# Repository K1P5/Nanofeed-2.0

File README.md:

# Nanofeed-2.0
Miniature Micro-controlled Feed Auger with Tank 

THIS IS A WORK IN PROGRESS! Thingiverse link: https://www.thingiverse.com/thing:4743999
------------------------------------------------------------------------------------------------------
Historic link to the orginal design, the Feederpi! 
https://www.thingiverse.com/thing:2947556

------------------------------------------------------------------------------------------------------------------------
I will continue to support this design based on user feedback; this means if no one is particularly interested, I will update only as I create new revisions to meet my personal project needs. If you have any questions, concerns, comments please feel free to message me and I will get back to you!

Remaining Uploads:

BOM
Assembly Instructions
PCB Schematic (Via Github link^^^)
Arduino Code (^^^)
Reference Build Images (^^^)

------------------------------------------------------------------------------------------------------------------------

This is the updated and improved miniature all-in-one material auger with integrated storage tank. Better torque, RTC (real time clock) control, Github hosted design/resource files, script(s), PCB files, etc! Based on an Arduino Nano, DRV8825 stepper driver, and a DS3231 RTC breakout, this unit is intended to be a low cost, fun, and DIY solution to automating your low-scale material handling (feeding) needs! 

Operation is simple; Fill the integrated tank with the material of choice (flake/granular material ~3-5mm Dia. MAX). Mount the unit in the location/orientation of choice, and provide 12V DC power via the rear power port. The Nanofeed will await a button press, upon which the auger will perform an adjustable feed cycle (adjustable via IDE). When the cycle is complete, the RTC module will begin a twenty-four (24) hour delay cycle (adjustable via IDE). After the elapsed time has passed, the Nanofeed will dispense an additional feed volume, resetting the RTC timer once again to continue your established, timed feed cycle. 

This design is the latest revision of my earlier Feederpi, the Pi Zero controlled feed system, with many improved features. 

-Arduino Nano powered; allows for a simple, low-cost microcontroller to handle automation, no need to waste a much more valuable and resource-intensive Pi.
 
-The belt path has been revised, ensuring sufficient torque transfer even when dispensing tough materials. 

-The original continuous-servo was replaced with a 4-wire miniature stepper motor, controlled via the onboard DRV8825. 

-Critical components are now mounted and assembled via "mounting cards"; Easy to print, assemble and disassemble the cards allow easy access and transfer of critical components. 

-Simplified and easy-to-print design ensures most if not all home printer solutions will have no issue reproducing the design in your own corner of the world. 

------------------------------------------------------------------------------------------------------------------------
Please Note!

This design utilizes a prototyped PCB, check the included images to understand the scope of development work involved. There "should" be sufficient interior volume within the PCB containment area, so it may be possible to revise the PCB mounting card to instead utilize a prototyping breadboard and related hardware. Check the related Parasolid file(s) to revise as needed.

I will release my original bare PCB, which will be available off of PCBWay for those that would like a more accessible option. The schematic, Gerber files and BOM will also be uploaded to Github, as I continue distributing this design. Please either check back here for the Github link or message me directly!

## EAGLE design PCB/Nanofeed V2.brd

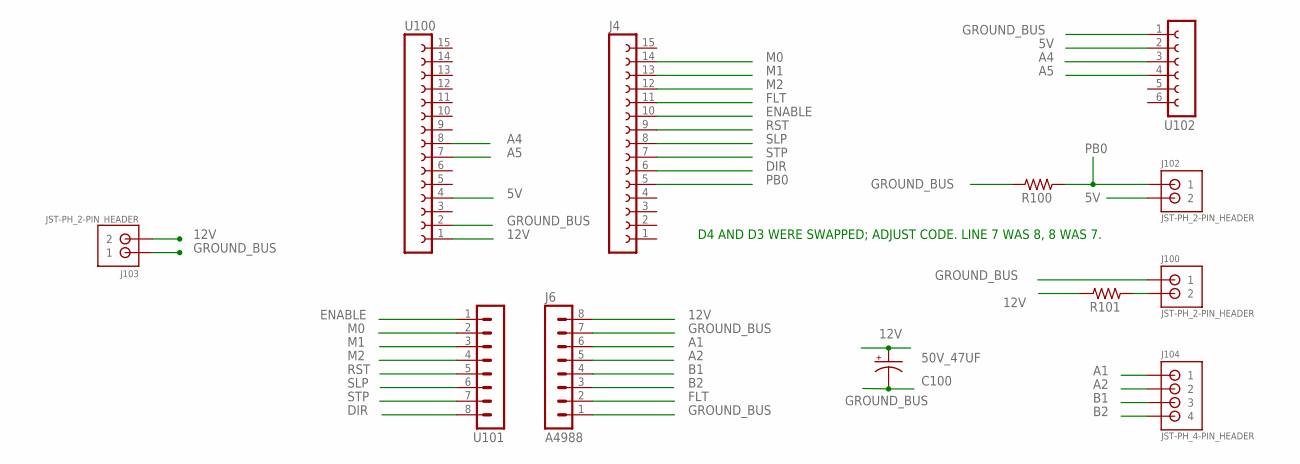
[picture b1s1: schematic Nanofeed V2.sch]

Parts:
C100: 50V_47UF; PANASONIC_D
J4: FE15-1; FE15
J6: A4988; MA08-1
J100, J102, J103: JST-PH_2-PIN_HEADER; JST_B2B-PH_HEADER
J104: JST-PH_4-PIN_HEADER; JST_B4B-PH_HEADER
R100, R101: R_5025; R5025
U100: FE15-1; FE15
U101: MA08-1
U102: FE06-1; FE06

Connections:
5V: J102.P2 (2), U100.4, U102.2
12V: C100.+, J6.8, J103.P2 (2), R101.2, U100.1
A1: J6.6, J104.P1 (1)
A2: J6.5, J104.P2 (2)
A4: U100.8, U102.3
A5: U100.7, U102.4
B1: J6.4, J104.P3 (3)
B2: J6.3, J104.P4 (4)
DIR: J4.6, U101.8
ENABLE: J4.10, U101.1
FLT: J4.11, J6.2
GROUND_BUS: C100.-, J6.1, J100.P1 (1), J103.P1 (1), R100.2, U100.2, U102.1
M0: J4.14, U101.2
M1: J4.13, U101.3
M2: J4.12, U101.4
unnamed: J100.P2 (2), R101.1
PB0: J4.5, J102.P1 (1), R100.1
RST: J4.9, U101.5
SLP: J4.8, U101.6
STP: J4.7, U101.7

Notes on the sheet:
D4 AND D3 WERE SWAPPED; ADJUST CODE. LINE 7 WAS 8, 8 WAS 7.

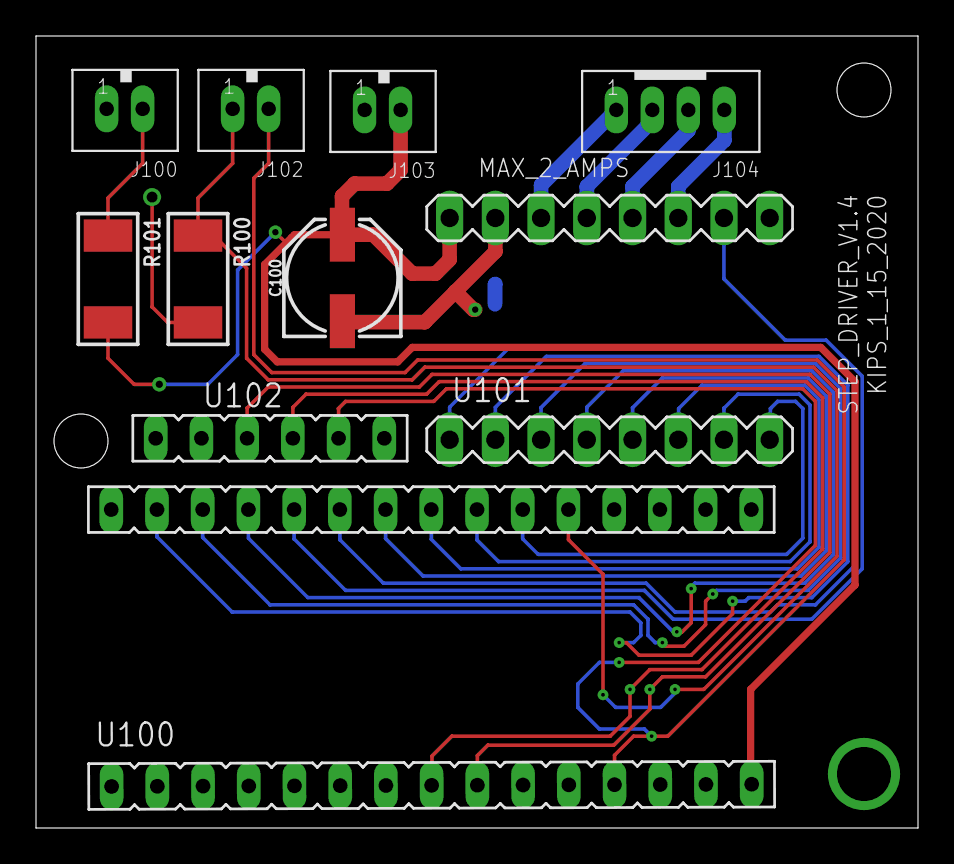
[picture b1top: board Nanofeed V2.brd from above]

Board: 2 copper layers, 49.0 x 44.0 mm, 12 parts (0 on the bottom side), 20 nets.

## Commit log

2021-01-30 Create ignore
2021-01-30 Create Nanofeed Script 00_1_30_2021_KIP5
2021-01-30 Added initial reference images
2021-01-30 Initial release of Rev00_2019 PCB
    Eagle files only; missing Gerber zip.
2021-01-30 Initial parasolid release
    Released for expediency; Rework required.
2021-01-30 Initial commit of STL files.
2021-01-30 Revised original commit of parasolid assembly.
2021-01-30 Added cropped reference images.
2021-01-31 Rename Nanofeed Script 00_1_30_2021_KIP5 to Nanofeed Beta Script 00_1_30_2021_KIP5
2021-01-31 Create Nanofeed Script 01_1_31_2021_KIP5
2021-02-14 Create Notes
2021-02-14 Add files via upload
    Initial upload of gerber files.

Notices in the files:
parts and their libraries:
SparkFun-Capacitors: Licensing: Creative Commons ShareAlike 4.0 International - https://creativecommons.org/licenses/by-sa/4.0
rc-master-smd: Copyright (C) 2007, Bob Starr
